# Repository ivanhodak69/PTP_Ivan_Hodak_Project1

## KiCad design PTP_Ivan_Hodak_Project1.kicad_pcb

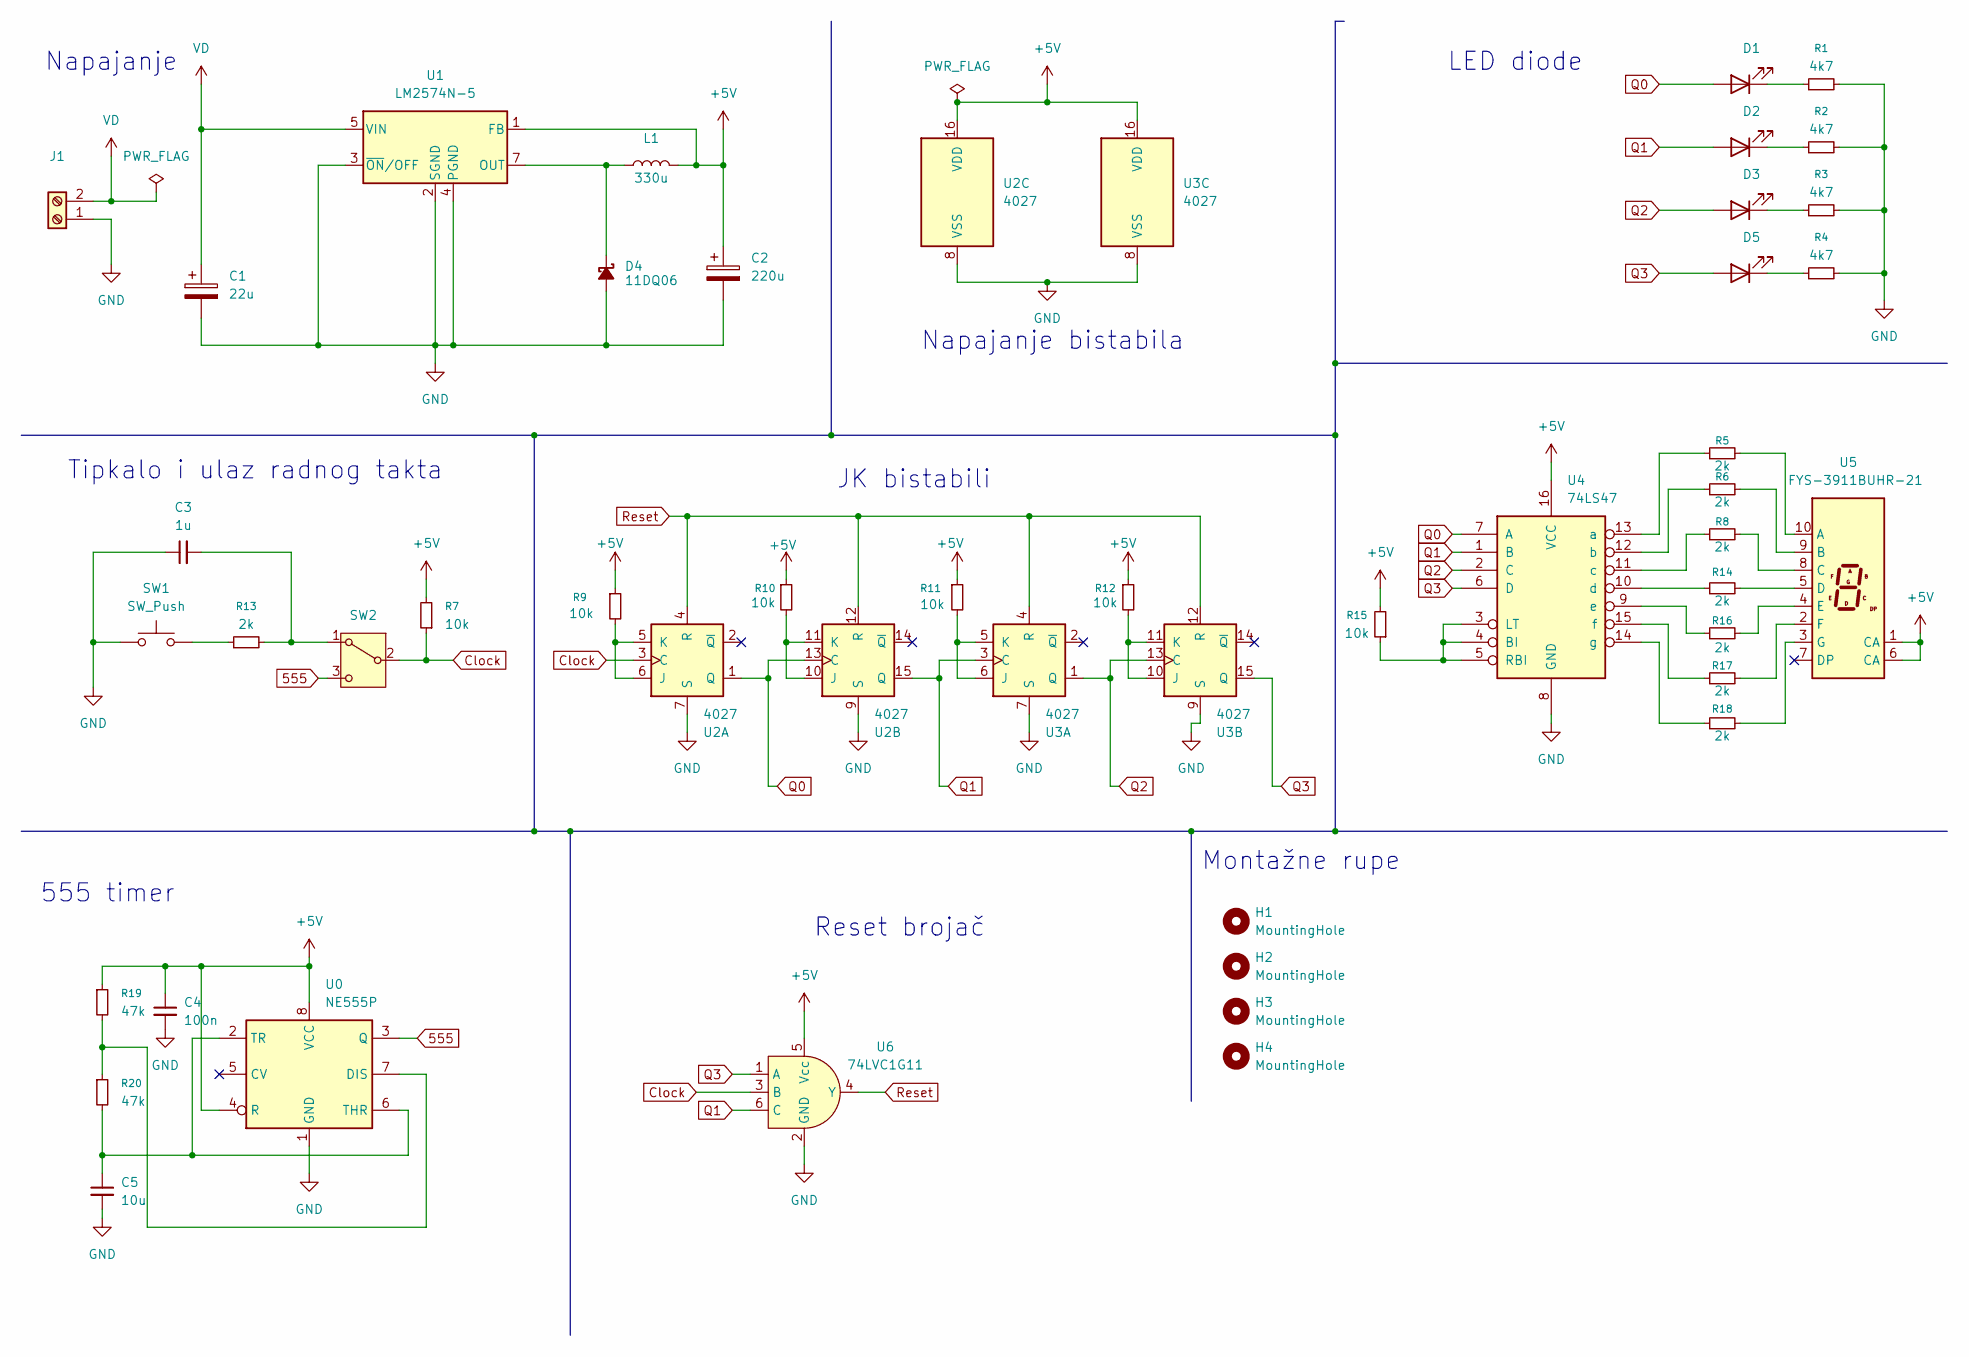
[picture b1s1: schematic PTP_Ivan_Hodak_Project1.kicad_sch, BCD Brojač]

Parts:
C1: 22u; CP_Radial_D5.0mm_P2.00mm; Manufacturer part number EWH1EM220D11OT
C2: 220u; CP_Radial_D5.0mm_P2.00mm; Manufacturer part number RD1A227M05011BB
C3: 1u; C_1206_3216Metric_Pad1.33x1.80mm_HandSolder; Manufacturer part number CL31B105KBHNNNE
C4: 100n; C_1206_3216Metric_Pad1.33x1.80mm_HandSolder; Manufacturer part number CL31B104KBCNNNC
C5: 10u; C_1206_3216Metric_Pad1.33x1.80mm_HandSolder; Manufacturer part number CL31A106KBHNNNE
D1, D2, D3, D5: LED; LED_D5.0mm
D4: 11DQ06; D_DO-41_SOD81_P12.70mm_Horizontal; Manufacturer part number 11DQ06TA
H1, H2, H3, H4: MountingHole; MountingHole_5.5mm
J1: TerminalBlock_MetzConnect_Type011_RT05502HBLC_1x02_P5.00mm_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; Manufacturer part number DG301-5.0-02P-12-00A(H)
L1: 330u; L_Radial_D7.2mm_P3.00mm_Murata_1700; Manufacturer part number COIL0608-0.33
R1, R2, R3, R4: 4k7; R_Axial_DIN0207_L6.3mm_D2.5mm_P10.16mm_Horizontal
R5, R6, R8, R14, R16, R17, R18: 2k; R_1206_3216Metric_Pad1.30x1.75mm_HandSolder; Manufacturer part number 1206S4F2001T5E
R7, R9, R10, R11, R12, R15: 10k; R_1206_3216Metric_Pad1.30x1.75mm_HandSolder
R13: 2k
R19, R20: 47k; R_1206_3216Metric_Pad1.30x1.75mm_HandSolder; Manufacturer part number 1206S4J0473T5E
SW1: SW_Push; SW_PUSH_6mm_H4.3mm; Manufacturer part number TACT-64N-F
SW2: SW_SPDT; SW_Slide_SPDT_Straight_CK_OS102011MS2Q; Manufacturer part number OS102011MS2QN1C
U0: NE555P; DIP-8_W7.62mm; Manufacturer part number NE555P
U1: LM2574N-5; DIP-8_W7.62mm; Manufacturer part number LM2574N-5G
U2, U3: 4027; DIP-16_W7.62mm_Socket_LongPads; Manufacturer part number CD4027BMS
U4: 74LS47; DIP-16_W7.62mm_Socket_LongPads
U5: FYS-3911BUHR-21; HDSP-7401; Manufacturer part number FYS-3911BUHR-21
U6: 74LVC1G11; SOT-23-6; Manufacturer part number SN74LVC1G11DBVR

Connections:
555: SW2.3 (C), U0.3 (Q)
+5V: C2.1, C4.1, L1.2, R7.2, R9.1, R10.1, R11.1, R12.1, R15.2, R19.1, U0.4 (R), U0.8 (VCC), U1.1 (FB), U2.16 (VDD), U3.16 (VDD), U4.16 (VCC), U5.1 (CA), U5.6 (CA), U6.5 (Vcc)
Clock: R7.1, SW2.2 (B), U2.3 (C), U6.3 (B)
GND: C1.2, C2.2, C3.1, C4.2, C5.2, D4.2 (A), J1.1, R1.2, R2.2, R3.2, R4.2, SW1.1, U0.1 (GND), U1.2 (SGND), U1.3 (~ON/OFF), U1.4 (PGND), U2.7 (S), U2.8 (VSS), U2.9 (S), U3.7 (S), U3.8 (VSS), U3.9 (S), U4.8 (GND), U6.2 (GND)
unnamed: D1.1 (K), R1.1
unnamed: D2.1 (K), R2.1
unnamed: D3.1 (K), R3.1
unnamed: D4.1 (K), L1.1, U1.7 (OUT)
unnamed: D5.1 (K), R4.1
unnamed: R13.1, SW1.2
unnamed: C3.2, R13.2, SW2.1 (A)
unnamed: R19.2, R20.1, U0.7 (DIS)
unnamed: C5.1, R20.2, U0.2 (TR), U0.6 (THR)
unnamed: R9.2, U2.5 (K), U2.6 (J)
unnamed: R10.2, U2.10 (J), U2.11 (K)
unnamed: R11.2, U3.5 (K), U3.6 (J)
unnamed: R12.2, U3.10 (J), U3.11 (K)
unnamed: R15.1, U4.3 (LT), U4.4 (BI), U4.5 (RBI)
unnamed: R5.1, U4.13 (a)
unnamed: R6.1, U4.12 (b)
unnamed: R8.1, U4.11 (c)
unnamed: R14.1, U4.10 (d)
unnamed: R16.1, U4.9 (e)
unnamed: R17.1, U4.15 (f)
unnamed: R18.1, U4.14 (g)
unnamed: R5.2, U5.10 (A)
unnamed: R6.2, U5.9 (B)
unnamed: R8.2, U5.8 (C)
unnamed: R14.2, U5.5 (D)
unnamed: R16.2, U5.4 (E)
unnamed: R17.2, U5.2 (F)
unnamed: R18.2, U5.3 (G)
Q0: D1.2 (A), U2.1 (Q), U2.13 (C), U4.7 (A)
Q1: D2.2 (A), U2.15 (Q), U3.3 (C), U4.1 (B), U6.6 (C)
Q2: D3.2 (A), U3.1 (Q), U3.13 (C), U4.2 (C)
Q3: D5.2 (A), U3.15 (Q), U4.6 (D), U6.1 (A)
Reset: U2.4 (R), U2.12 (R), U3.4 (R), U3.12 (R), U6.4 (Y)
VD: C1.1, J1.2, U1.5 (VIN)

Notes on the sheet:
Napajanje bistabila
LED diode
Napajanje
Tipkalo i ulaz radnog takta
JK bistabili
Reset brojač
Montažne rupe
555 timer

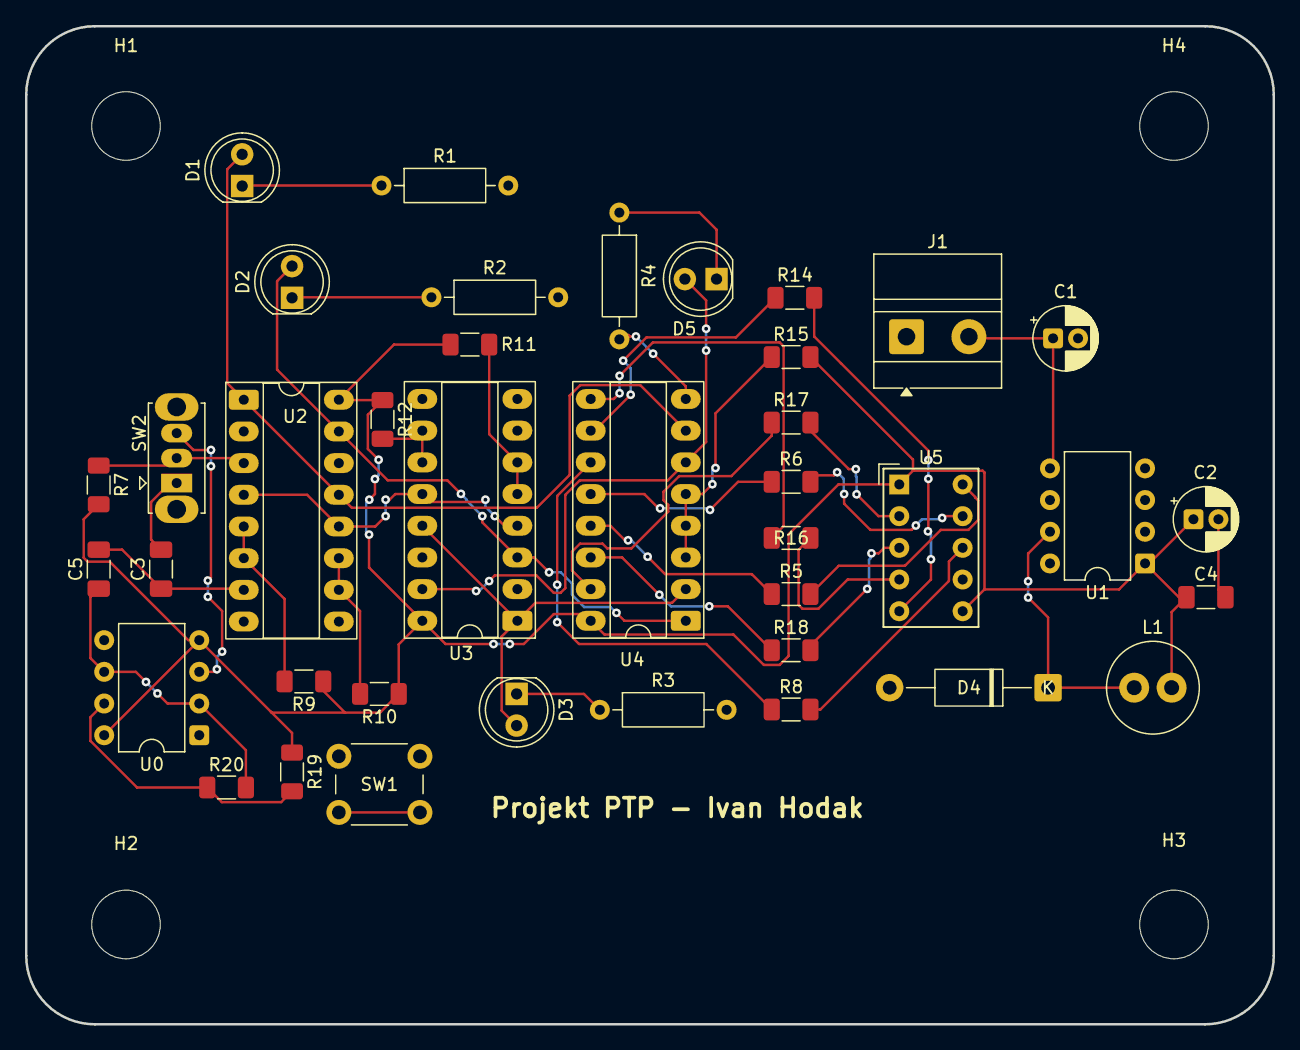
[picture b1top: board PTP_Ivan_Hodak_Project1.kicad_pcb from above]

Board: 2 copper layers, 100.0 x 80.0 mm, 43 parts (0 on the bottom side), 37 nets.

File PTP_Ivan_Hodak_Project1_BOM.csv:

Reference;Qty;Value;Footprint;Datasheet;Manufacturer;Manufacturer part number
C1;1;22u;Capacitor_THT:CP_Radial_D5.0mm_P2.00mm;~;AISHI;EWH1EM220D11OT
C2;1;220u;Capacitor_THT:CP_Radial_D5.0mm_P2.00mm;~;SAMWHA;RD1A227M05011BB
C3;1;1u;Capacitor_SMD:C_1206_3216Metric_Pad1.33x1.80mm_HandSolder;~;SAMSUNG;CL31B105KBHNNNE
C4;1;100n;Capacitor_SMD:C_1206_3216Metric_Pad1.33x1.80mm_HandSolder;~;SAMSUNG;CL31B104KBCNNNC
C5;1;10u;Capacitor_SMD:C_1206_3216Metric_Pad1.33x1.80mm_HandSolder;~;SAMSUNG;CL31A106KBHNNNE
D1,D2,D3,D5;4;LED;LED_THT:LED_D5.0mm;~;;
D4;1;11DQ06;Diode_THT:D_DO-41_SOD81_P12.70mm_Horizontal;~;SMC DIODE SOLUTIONS;11DQ06TA
H1,H2,H3,H4;4;MountingHole;MountingHole:MountingHole_5.5mm;~;;
J1;1;~;TerminalBlock_MetzConnect:TerminalBlock_MetzConnect_Type011_RT05502HBLC_1x02_P5.00mm_Horizontal;~;DEGSON ELECTRONICS;DG301-5.0-02P-12-00A(H)
L1;1;330u;Inductor_THT:L_Radial_D7.2mm_P3.00mm_Murata_1700;~;FERROCORE;COIL0608-0.33
R1,R2,R3,R4;4;4k7;Resistor_THT:R_Axial_DIN0207_L6.3mm_D2.5mm_P10.16mm_Horizontal;~;;
R5,R6,R14,R16,R17,R18;6;2k;Resistor_SMD:R_1206_3216Metric_Pad1.30x1.75mm_HandSolder;~;ROYALOHM;1206S4F2001T5E
R7,R9,R10,R11,R12,R15;6;10k;Resistor_SMD:R_1206_3216Metric_Pad1.30x1.75mm_HandSolder;~;ROYALOHM;1206S4J0473T5E
R8;1;2k;Resistor_SMD:R_1206_3216Metric_Pad1.30x1.75mm_HandSolder;~;ROYALOHM;1206S4F2001T5E
R13;1;2k;Resistor_SMD:R_1206_3216Metric_Pad1.30x1.75mm_HandSolder;~;ROYALOHM;1206S4F2001T5E
R19,R20;2;47k;Resistor_SMD:R_1206_3216Metric_Pad1.30x1.75mm_HandSolder;~;ROYALOHM;1206S4J0473T5E
SW1;1;SW_Push;Button_Switch_THT:SW_PUSH_6mm_H4.3mm;~;microswitch TACT;TACT-64N-F
SW2;1;SW_SPDT;Button_Switch_THT:SW_Slide_SPDT_Straight_CK_OS102011MS2Q;~;C&K;OS102011MS2QN1C
U0;1;NE555P;Package_DIP:DIP-8_W7.62mm;http://www.ti.com/lit/ds/symlink/ne555.pdf;TEXAS INSTRUMENTS;NE555P
U1;1;LM2574N-5;Package_DIP:DIP-8_W7.62mm;http://www.national.com/ds/LM/LM2574.pdf;;LM2574N-5G
U2,U3;2;4027;Package_DIP:DIP-16_W7.62mm_Socket_LongPads;http://www.intersil.com/content/dam/Intersil/documents/cd40/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;RENESAS;CD4027BMS
U4;1;74LS47;Package_DIP:DIP-16_W7.62mm_Socket_LongPads;http://www.ti.com/lit/gpn/sn74LS47;TEXAS INSTRUMENTS;
U5;1;FYS-3911BUHR-21;Display_7Segment:HDSP-7401;https://docs.broadcom.com/docs/AV02-2553EN;FORYARD;FYS-3911BUHR-21
U6;1;74LVC1G11;SOT23-6:SOT-23-6;https://www.ti.com/lit/ds/symlink/tps64202.pdf?ts=1770009256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;TEXAS INSTRUMENTS;SN74LVC1G11DBVR

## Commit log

2025-10-21 ispunjena sastavnica
2025-10-28 Dodali komponente
2025-11-04 LV3 overwrite
2025-11-11 Shema - gotova
2025-11-11 Shema - Citanje iz Excela
2025-11-11 Shema
2025-12-09 PCB Update
2025-12-16 Update projekta
